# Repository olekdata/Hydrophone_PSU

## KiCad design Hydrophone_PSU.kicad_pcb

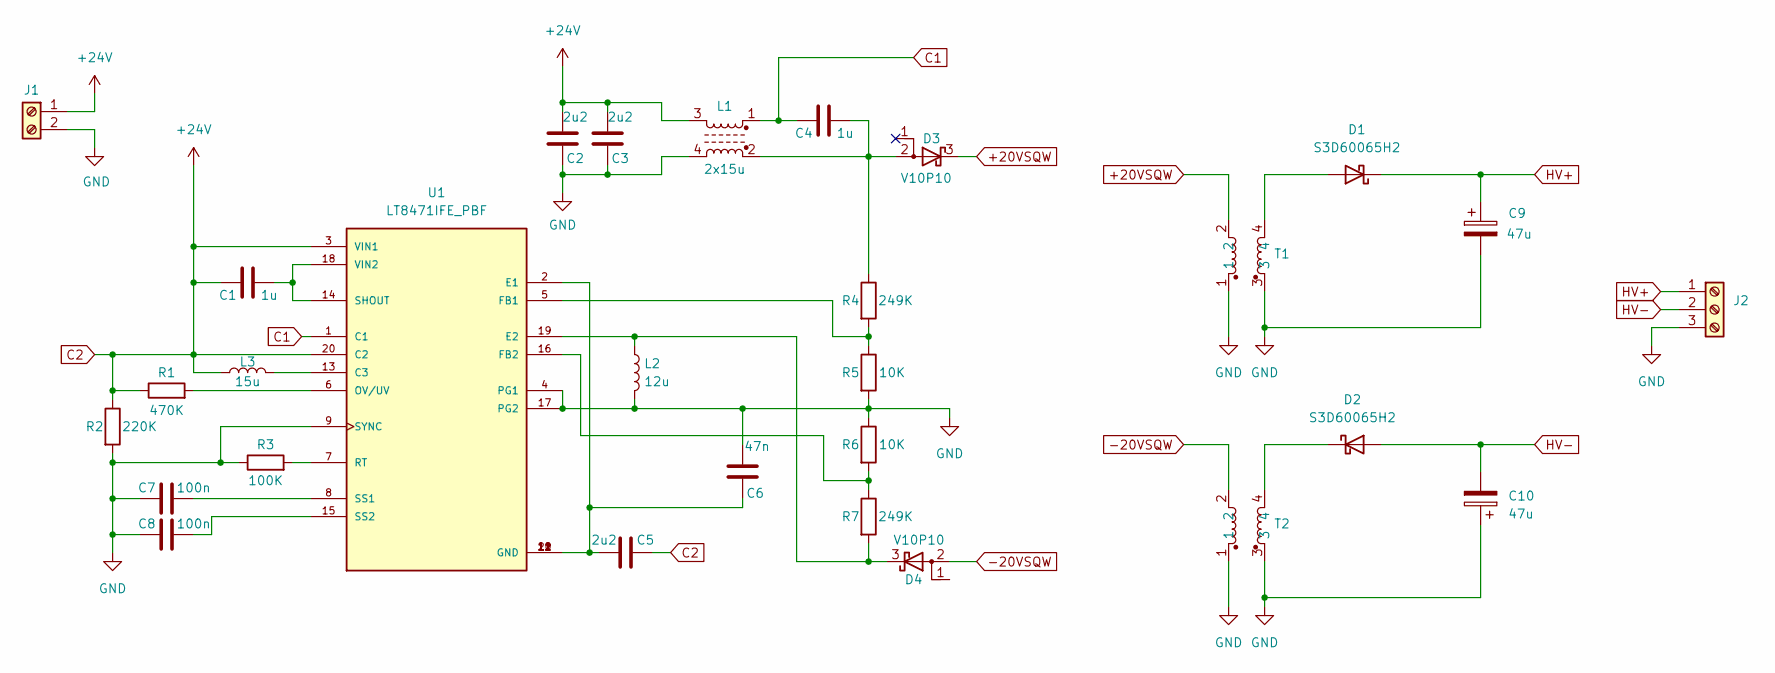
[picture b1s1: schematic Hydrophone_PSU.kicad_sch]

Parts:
C1, C4: 1u; C_1206_3216Metric
C2, C3, C5: 2u2; C_1206_3216Metric
C6: 47n; C_0603_1608Metric
C7, C8: 100n; C_0603_1608Metric
C9, C10: 47u; CP_Elec_16x17.5
D1, D2: S3D60065H2; TO-247-2_Horizontal_TabDown
D3, D4: V10P10; TO-277A
J1: Screw_Terminal_01x02; TerminalBlock_Altech_AK300-2_P5.00mm
J2: Screw_Terminal_01x03; TerminalBlock_Altech_AK300-3_P5.00mm
L1: 2x15u; L_Wuerth_WE-DD-Typ-M-Typ-S
L2: 12u; L_12x12mm_H8mm
L3: 15u; L_7.3x7.3_H4.5
R1: 470K; R_0603_1608Metric
R2: 220K; R_0603_1608Metric
R3: 100K; R_0805_2012Metric
R4, R7: 249K; R_0603_1608Metric
R5, R6: 10K; R_0603_1608Metric
T1, T2: PLANAR_HYDROPHONE_TRANSFORMER
U1: LT8471IFE_PBF; SOP65P640X120-21N; PARTREV D

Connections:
+20VSQW: D3.3 (K), T1.2
-20VSQW: D4.2 (A), T2.2
C1: C4.1, L1.1, U1.1 (C1)
C2: C1.1, C2.2, C3.2, C5.1, J1.1, L1.3, L3.1, R1.1, R2.1, U1.3 (VIN1), U1.20 (C2)
HV+: C9.1, D1.1 (K), J2.1
HV-: C10.2, D2.2 (A), J2.2
unnamed: C4.2, D3.2 (A), L1.2, R4.1
unnamed: D1.2 (A), T1.4
unnamed: D2.1 (K), T2.4
unnamed: D4.3 (K), L2.1, R7.2, U1.19 (E2)
unnamed: L3.2, U1.13 (C3)
unnamed: R4.2, R5.1, U1.5 (FB1)
unnamed: R6.2, R7.1, U1.16 (FB2)
unnamed: R1.2, U1.6 (OV/UV)
unnamed: R3.2, U1.7 (RT)
unnamed: C1.2, U1.14 (SHOUT), U1.18 (VIN2)
unnamed: C7.2, U1.8 (SS1)
unnamed: C8.2, U1.15 (SS2)

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
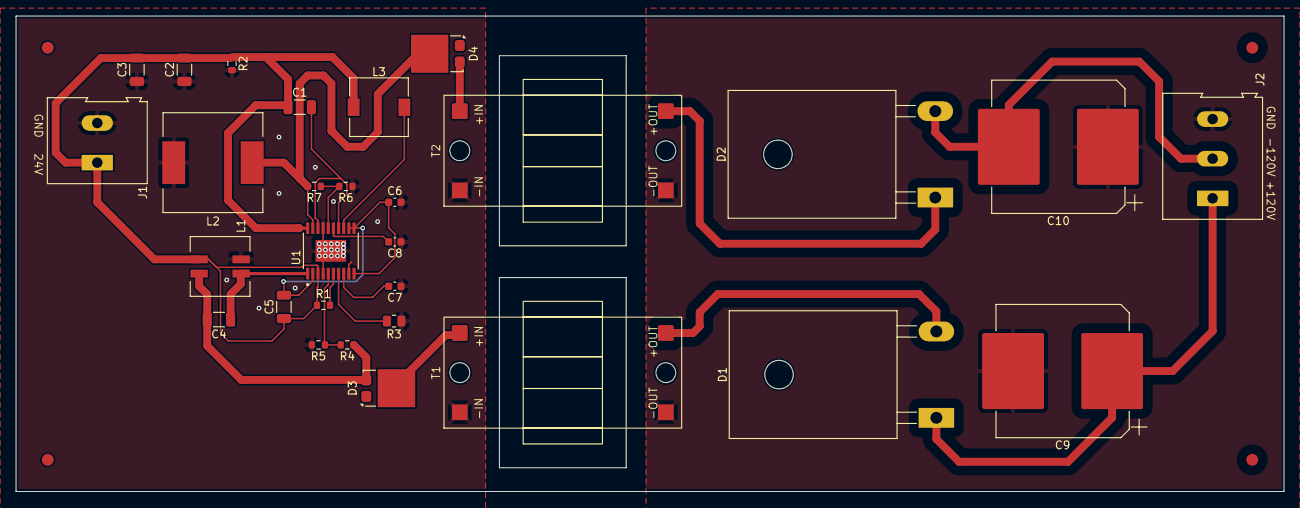
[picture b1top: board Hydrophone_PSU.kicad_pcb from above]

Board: 2 copper layers, 160.0 x 60.0 mm, 29 parts (0 on the bottom side), 20 nets.

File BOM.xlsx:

| COMPONENT LIST TEMPLATE
 | Symbol na sch. | Nazwa | Link | Ilość na płytce (zalecany nadmiar) | Uwagi
 | U1 | LT8471IFE#PBF | https://www.mouser.pl/ProductDetail/Analog-Devices/LT8471IFE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 | 1
 | L1 (2x15u) | DRQ74-150-R | https://www.mouser.pl/ProductDetail/Eaton-Electronics/DRQ74-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 | 1
 | L2 (12u) | DE1207-12 | https://www.tme.eu/pl/details/de1207-12/dlawiki/ferrocore/ | 1
 | L3 (15u) | DE0704-15 | https://www.tme.eu/pl/details/de0704-15/dlawiki/ferrocore/ | 1
 | C1, C4 (1u/100 V) | CL31B105KCHNNNE | https://www.tme.eu/pl/details/cl31b105kchnnne/kondensatory-m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 | 2
 | C2, C3, C5 (2u2) | CL31B225KBHNNNE | https://www.tme.eu/pl/details/cl31b225kbhnnne/kondensatory-m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 | 3
 | C6 (47n) | CL10B473KB8NNNC | https://www.tme.eu/pl/details/cl10b473kb8nnnc/kondensatory-m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 | 1
 | C7, C8 (100n) | CL10B104KB8NNNC | https://www.tme.eu/pl/details/cl10b104kb8nnnc/kondensatory-m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 | 2
 | C9, C10 (47u/250V) | EDH476M250A9TAA | https://www.mouser.pl/ProductDetail/KEMET/EDH476M250A9TAA?qs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 | 2 | Na TME brak w magazynie i długi LT
 | R1 (470K) | 0603SAF4703T5E | https://www.tme.eu/pl/details/smd0805-470r-1%25/rezystory-sm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 | 1
 | R2 (220K) | 0603SAF2203T5E | https://www.tme.eu/pl/details/smd0603-220k-1%25/rezystory-sm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 | 1
 | R3 (100K) | 0805S8F1003T5E | https://www.tme.eu/pl/details/smd0805-100k-1%25/rezystory-sm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 | 1
 | R4, R7 (249K) | 0603SAF2493T5E | https://www.tme.eu/pl/details/era3aeb2433v/rezystory-smd/panasonic/ | 2
 | R5, R6 (10K) | 0603SAF1002T5E | https://www.tme.eu/pl/details/smd0603-10k-1%25/rezystory-smd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 | 2
 | D1, D2 (650 V, 484 W) | S3D60065H2 | https://www.tme.eu/pl/details/s3d60065h2-smc/diody-schottky-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 | 2 | THT
 | J1 | DG128-5.0-02P14 | https://www.tme.eu/pl/details/dg128-5.0-02p14/listwy-zacisko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 | 1 | THT
 | J2 (400V) | MKDSN2.5/3-5.08 | https://www.tme.eu/pl/details/mkdsn2.5_3-5.08/listwy-zacisko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 | 1
 | T1, T2 - rdzenie | B66283G0000X187 | https://www.tme.eu/pl/details/b66283g0000x187/rdzenie-ferryt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 | 4
 | D3, D4 (100 V, 10 A) | V10P10 | https://www.tme.eu/pl/details/v10p10-m3_86a/diody-schottky-s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 | 2
 | CLICK HERE TO CREATE IN SMARTSHEET

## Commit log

2025-12-05 init
2025-12-05 poprawki Tadeusz
2025-12-05 poprawki Olek.
